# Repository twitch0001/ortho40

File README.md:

# ortho40
 40%  ortho with a display in the middle

Inspired by [ChrisChrisLoLo/keezyboost40](https://github.com/ChrisChrisLoLo/keezyboost40)  (i just need more keys lol)

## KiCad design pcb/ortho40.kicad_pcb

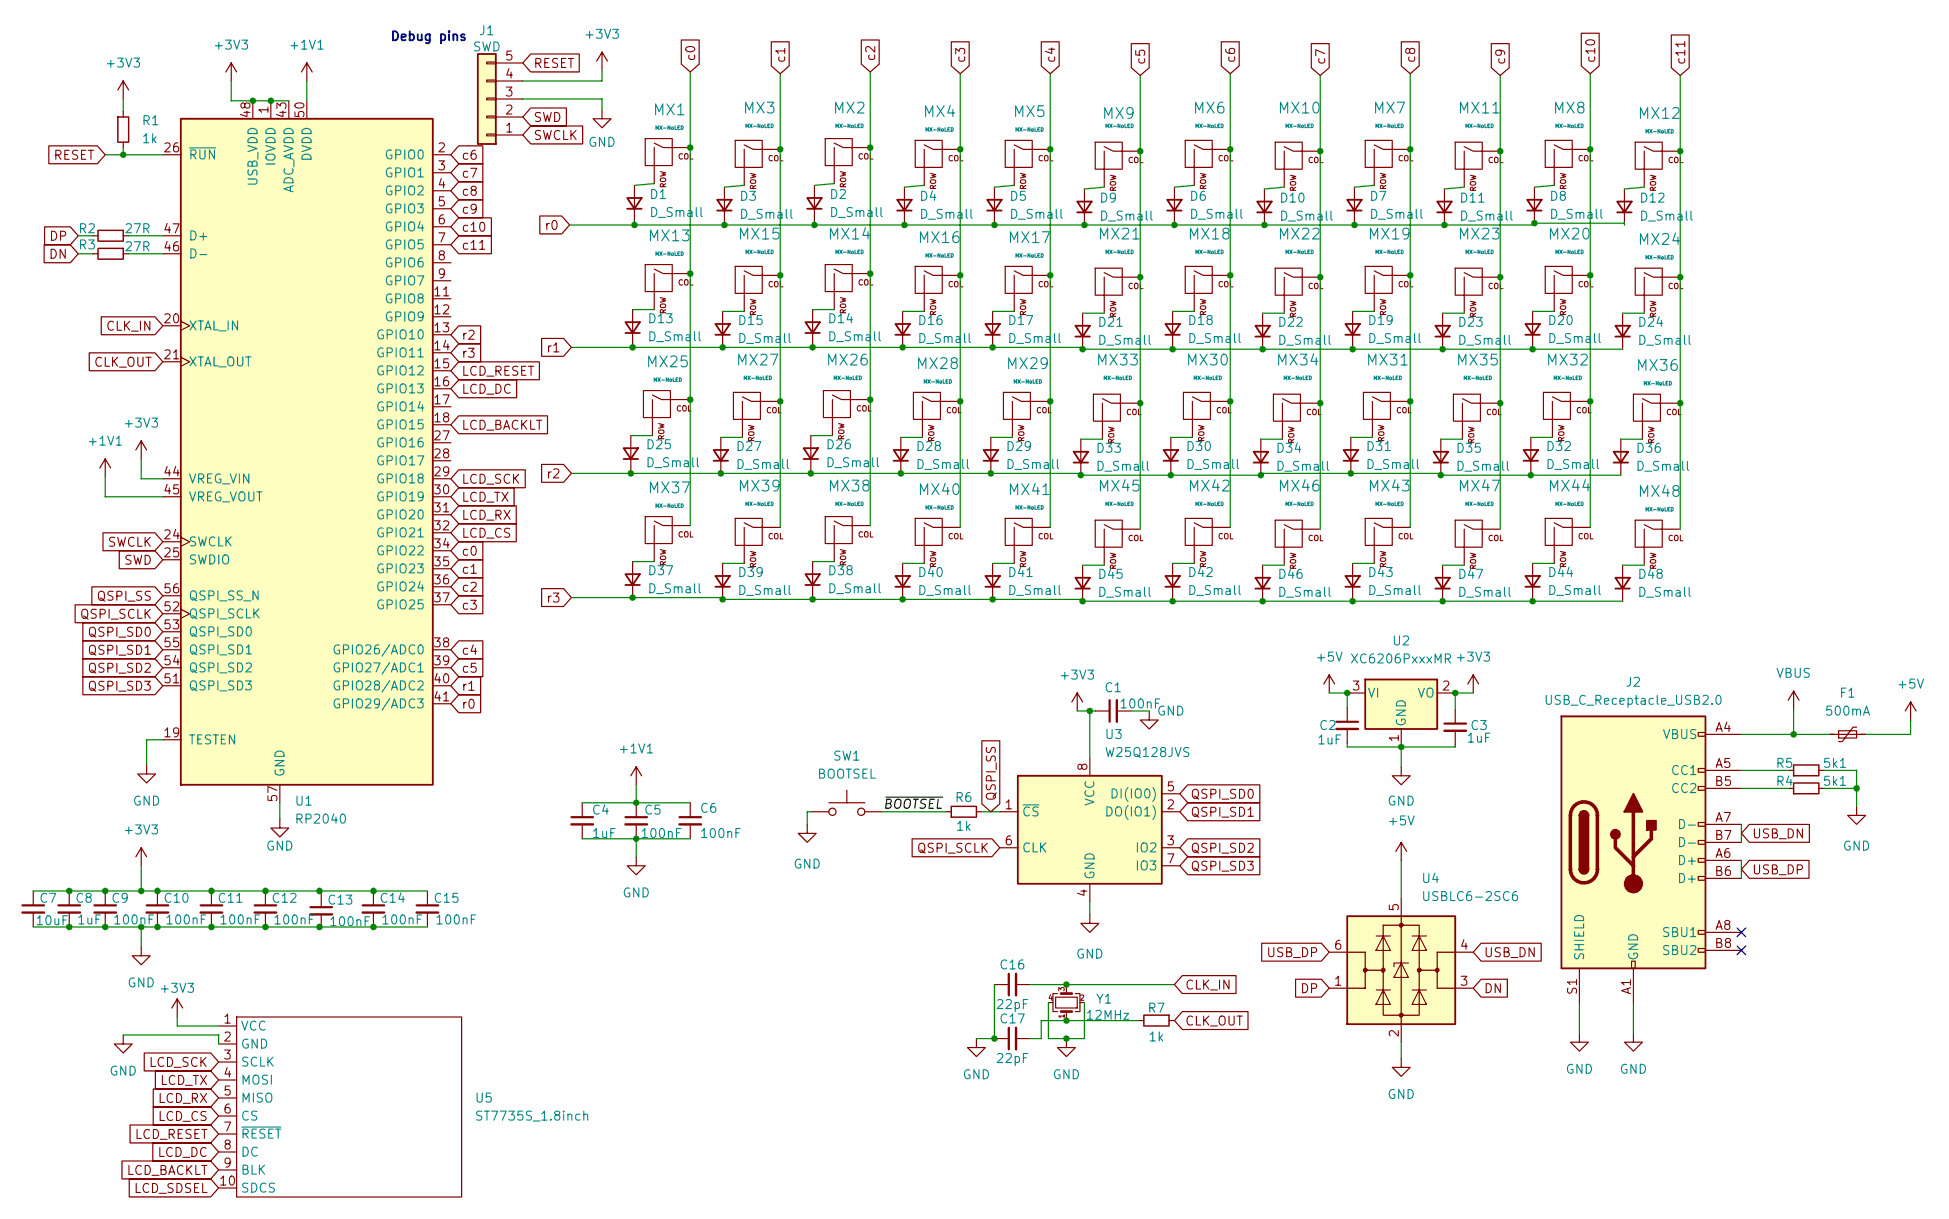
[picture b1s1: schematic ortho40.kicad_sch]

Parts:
C1, C5, C6, C9, C10, C11, C12, C13, C14, C15: 100nF; C_0402_1005Metric
C2, C3, C4, C8: 1uF; C_0402_1005Metric
C7: 10uF; C_0402_1005Metric
C16, C17: 22pF; C_0402_1005Metric
D1, D2, D3, D4, D5, D6, D7, D8, D9, D10, D11, D12, D13, D14, D15, D16, D17, D18, D19, D20, D21, D22, D23, D24, D25, D26, D27, D28, D29, D30, D31, D32, D33, D34, D35, D36, D37, D38, D39, D40, D41, D42, D43, D44, D45, D46, D47, D48: D_Small; D_SOD-123
F1: 500mA; Fuse_1206_3216Metric
J1: SWD; PinSocket_1x05_P2.54mm_Vertical
J2: USB_C_Receptacle_USB2.0; USB_C_Receptacle_HRO_TYPE-C-31-M-12
MX1, MX2, MX3, MX4, MX5, MX6, MX7, MX8, MX9, MX10, MX11, MX12, MX13, MX14, MX15, MX16, MX17, MX18, MX19, MX20, MX21, MX22, MX23, MX24, MX25, MX26, MX27, MX28, MX29, MX30, MX31, MX32, MX33, MX34, MX35, MX36, MX37, MX38, MX39, MX40, MX41, MX42, MX43, MX44, MX45, MX46, MX47, MX48: MX-NoLED; MX-1U-NoLED
R1, R6, R7: 1k; R_0402_1005Metric
R2, R3: 27R; R_0402_1005Metric
R4, R5: 5k1; R_0402_1005Metric
SW1: BOOTSEL; SW_Push_SPST_NO_Alps_SKRK
U1: RP2040; RP2040-QFN-56
U2: XC6206PxxxMR; SOT-23
U3: W25Q128JVS; SOIC-8_5.23x5.23mm_P1.27mm
U4: USBLC6-2SC6; SOT-23-6
U5: ST7735S_1.8inch; DFR0928
Y1: 12MHz; Crystal_SMD_3225-4Pin_3.2x2.5mm

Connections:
+1V1: C4.1, C5.1, C6.1, U1.23 (DVDD), U1.45 (VREG_VOUT), U1.50 (DVDD)
+3V3: C1.1, C3.1, C7.1, C8.1, C9.1, C10.1, C11.1, C12.1, C13.1, C14.1, C15.1, J1.4, R1.1, U1.1 (IOVDD), U1.10 (IOVDD), U1.22 (IOVDD), U1.33 (IOVDD), U1.42 (IOVDD), U1.43 (ADC_AVDD), U1.44 (VREG_VIN), U1.48 (USB_VDD), U1.49 (IOVDD), U2.2 (VO), U3.8 (VCC), U5.1 (VCC)
+5V: C2.1, F1.2, U2.3 (VI), U4.5 (VBUS)
/~BOOTSEL: R6.1, SW1.2
CLK_IN: C16.2, U1.20 (XTAL_IN), Y1.3
CLK_OUT: R7.1, U1.21 (XTAL_OUT)
DN: R3.2, U4.3 (I/O2)
DP: R2.2, U4.1 (I/O1)
GND: C1.2, C2.2, C3.2, C4.2, C5.2, C6.2, C7.2, C8.2, C9.2, C10.2, C11.2, C12.2, C13.2, C14.2, C15.2, C16.1, C17.1, J1.3, J2.A1 (GND), J2.A12 (GND), J2.B1 (GND), J2.B12 (GND), J2.S1 (SHIELD), R4.2, R5.2, SW1.1, U1.19 (TESTEN), U1.57 (GND), U2.1 (GND), U3.4 (GND), U4.2 (GND), U5.2 (GND), Y1.2, Y1.4
LCD_BACKLT: U1.18 (GPIO15), U5.9 (BLK)
LCD_CS: U1.32 (GPIO21), U5.6 (CS)
LCD_DC: U1.16 (GPIO13), U5.8 (DC)
LCD_RESET: U1.15 (GPIO12), U5.7 (~RESET)
LCD_RX: U1.31 (GPIO20), U5.5 (MISO)
LCD_SCK: U1.29 (GPIO18), U5.3 (SCLK)
LCD_SDSEL: U5.10 (SDCS)
LCD_TX: U1.30 (GPIO19), U5.4 (MOSI)
unnamed: C17.2, R7.2, Y1.1
unnamed: D1.2 (A), MX1.2 (ROW)
unnamed: D2.2 (A), MX2.2 (ROW)
unnamed: D3.2 (A), MX3.2 (ROW)
unnamed: D4.2 (A), MX4.2 (ROW)
unnamed: D5.2 (A), MX5.2 (ROW)
unnamed: D6.2 (A), MX6.2 (ROW)
unnamed: D7.2 (A), MX7.2 (ROW)
unnamed: D8.2 (A), MX8.2 (ROW)
unnamed: D9.2 (A), MX9.2 (ROW)
unnamed: D10.2 (A), MX10.2 (ROW)
unnamed: D11.2 (A), MX11.2 (ROW)
unnamed: D12.2 (A), MX12.2 (ROW)
unnamed: D13.2 (A), MX13.2 (ROW)
unnamed: D14.2 (A), MX14.2 (ROW)
unnamed: D15.2 (A), MX15.2 (ROW)
unnamed: D16.2 (A), MX16.2 (ROW)
unnamed: D17.2 (A), MX17.2 (ROW)
unnamed: D18.2 (A), MX18.2 (ROW)
unnamed: D19.2 (A), MX19.2 (ROW)
unnamed: D20.2 (A), MX20.2 (ROW)
unnamed: D21.2 (A), MX21.2 (ROW)
unnamed: D22.2 (A), MX22.2 (ROW)
unnamed: D23.2 (A), MX23.2 (ROW)
unnamed: D24.2 (A), MX24.2 (ROW)
unnamed: D25.2 (A), MX25.2 (ROW)
unnamed: D26.2 (A), MX26.2 (ROW)
unnamed: D27.2 (A), MX27.2 (ROW)
unnamed: D28.2 (A), MX28.2 (ROW)
unnamed: D29.2 (A), MX29.2 (ROW)
unnamed: D30.2 (A), MX30.2 (ROW)
unnamed: D31.2 (A), MX31.2 (ROW)
unnamed: D32.2 (A), MX32.2 (ROW)
unnamed: D33.2 (A), MX33.2 (ROW)
unnamed: D34.2 (A), MX34.2 (ROW)
unnamed: D35.2 (A), MX35.2 (ROW)
unnamed: D36.2 (A), MX36.2 (ROW)
unnamed: D37.2 (A), MX37.2 (ROW)
unnamed: D38.2 (A), MX38.2 (ROW)
unnamed: D39.2 (A), MX39.2 (ROW)
unnamed: D40.2 (A), MX40.2 (ROW)
unnamed: D41.2 (A), MX41.2 (ROW)
unnamed: D42.2 (A), MX42.2 (ROW)
unnamed: D43.2 (A), MX43.2 (ROW)
unnamed: D44.2 (A), MX44.2 (ROW)
unnamed: D45.2 (A), MX45.2 (ROW)
unnamed: D46.2 (A), MX46.2 (ROW)
unnamed: D47.2 (A), MX47.2 (ROW)
unnamed: D48.2 (A), MX48.2 (ROW)
unnamed: J2.A5 (CC1), R4.1
unnamed: J2.B5 (CC2), R5.1
unnamed: R2.1, U1.47 (D+)
unnamed: R3.1, U1.46 (D-)
QSPI_SCLK: U1.52 (QSPI_SCLK), U3.6 (CLK)
QSPI_SD0: U1.53 (QSPI_SD0), U3.5 (DI(IO0))
QSPI_SD1: U1.55 (QSPI_SD1), U3.2 (DO(IO1))
QSPI_SD2: U1.54 (QSPI_SD2), U3.3 (IO2)
QSPI_SD3: U1.51 (QSPI_SD3), U3.7 (IO3)
QSPI_SS: R6.2, U1.56 (QSPI_SS_N), U3.1 (~CS)
RESET: J1.5, R1.2, U1.26 (~RUN)
SWCLK: J1.1, U1.24 (SWCLK)
SWD: J1.2, U1.25 (SWDIO)
USB_DN: J2.A7 (D-), J2.B7 (D-), U4.4 (I/O2)
USB_DP: J2.A6 (D+), J2.B6 (D+), U4.6 (I/O1)
VBUS: F1.1, J2.A4 (VBUS), J2.A9 (VBUS), J2.B4 (VBUS), J2.B9 (VBUS)
c0: MX1.1 (COL), MX13.1 (COL), MX25.1 (COL), MX37.1 (COL), U1.34 (GPIO22)
c1: MX3.1 (COL), MX15.1 (COL), MX27.1 (COL), MX39.1 (COL), U1.35 (GPIO23)
c2: MX2.1 (COL), MX14.1 (COL), MX26.1 (COL), MX38.1 (COL), U1.36 (GPIO24)
c3: MX4.1 (COL), MX16.1 (COL), MX28.1 (COL), MX40.1 (COL), U1.37 (GPIO25)
c4: MX5.1 (COL), MX17.1 (COL), MX29.1 (COL), MX41.1 (COL), U1.38 (GPIO26/ADC0)
c5: MX9.1 (COL), MX21.1 (COL), MX33.1 (COL), MX45.1 (COL), U1.39 (GPIO27/ADC1)
c6: MX6.1 (COL), MX18.1 (COL), MX30.1 (COL), MX42.1 (COL), U1.2 (GPIO0)
c7: MX10.1 (COL), MX22.1 (COL), MX34.1 (COL), MX46.1 (COL), U1.3 (GPIO1)
c8: MX7.1 (COL), MX19.1 (COL), MX31.1 (COL), MX43.1 (COL), U1.4 (GPIO2)
c9: MX11.1 (COL), MX23.1 (COL), MX35.1 (COL), MX47.1 (COL), U1.5 (GPIO3)
c10: MX8.1 (COL), MX20.1 (COL), MX32.1 (COL), MX44.1 (COL), U1.6 (GPIO4)
c11: MX12.1 (COL), MX24.1 (COL), MX36.1 (COL), MX48.1 (COL), U1.7 (GPIO5)
r0: D1.1 (K), D2.1 (K), D3.1 (K), D4.1 (K), D5.1 (K), D6.1 (K), D7.1 (K), D8.1 (K), D9.1 (K), D10.1 (K), D11.1 (K), D12.1 (K), U1.41 (GPIO29/ADC3)
r1: D13.1 (K), D14.1 (K), D15.1 (K), D16.1 (K), D17.1 (K), D18.1 (K), D19.1 (K), D20.1 (K), D21.1 (K), D22.1 (K), D23.1 (K), D24.1 (K), U1.40 (GPIO28/ADC2)
r2: D25.1 (K), D26.1 (K), D27.1 (K), D28.1 (K), D29.1 (K), D30.1 (K), D31.1 (K), D32.1 (K), D33.1 (K), D34.1 (K), D35.1 (K), D36.1 (K), U1.13 (GPIO10)
r3: D37.1 (K), D38.1 (K), D39.1 (K), D40.1 (K), D41.1 (K), D42.1 (K), D43.1 (K), D44.1 (K), D45.1 (K), D46.1 (K), D47.1 (K), D48.1 (K), U1.14 (GPIO11)

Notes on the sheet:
Debug pins

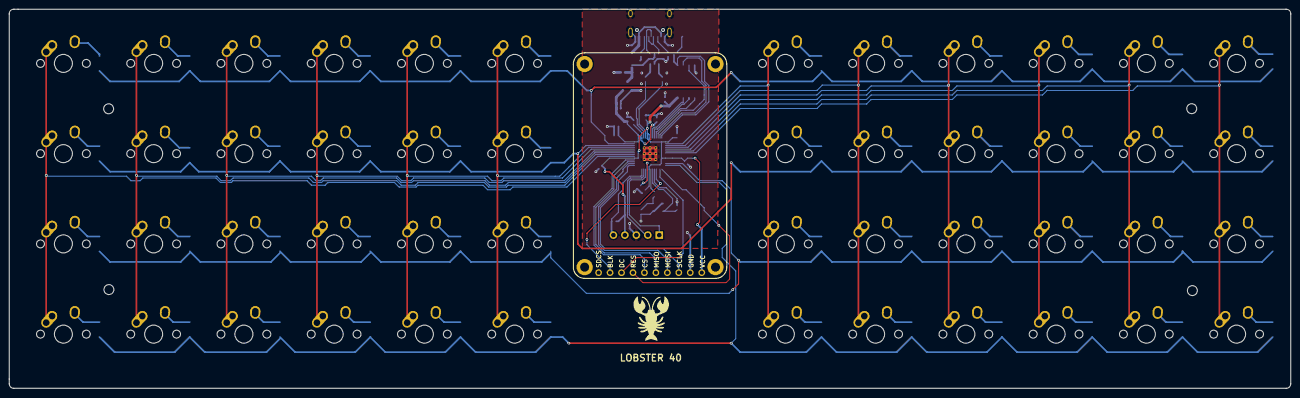
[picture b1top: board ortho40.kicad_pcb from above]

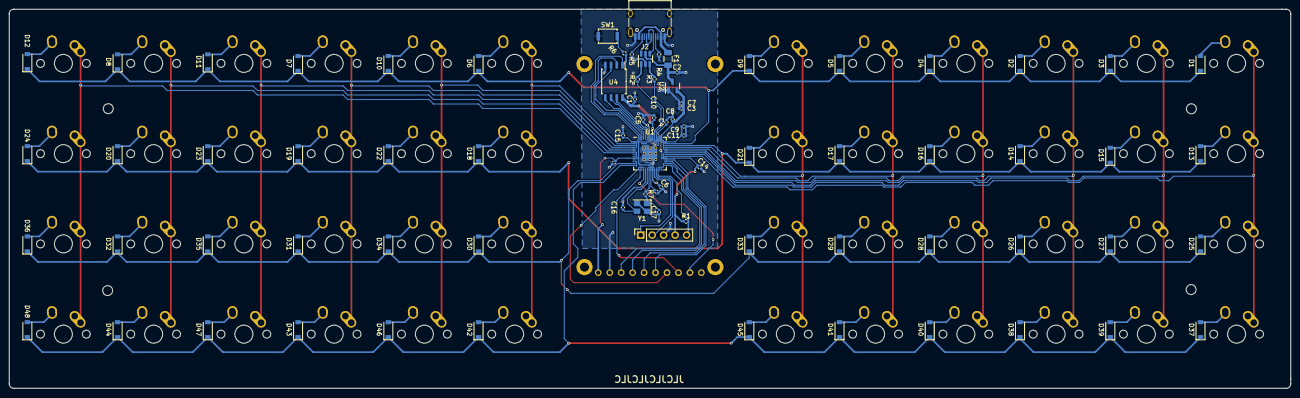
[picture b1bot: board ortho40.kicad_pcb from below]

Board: 2 copper layers, 284.0 x 84.0 mm, 134 parts (81 on the bottom side), 97 nets.

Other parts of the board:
MH1, MH2, MH3, MH4: MountingHole_2.2mm_M2

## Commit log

2022-08-17 Init kicad project
2022-08-17 Add submodules
2022-08-17 Import footprints
2022-08-17 Finish Matrix + Start RP2040 setup
2022-08-18 Schematic done
2022-08-19 blobpain
2022-08-21 Kindof finish pcb
2022-08-21 Move some things
2022-08-22 Fully finish PCB
2022-08-23 Setup Display
2022-08-23 Possibly fix nets?
    I'm not sure but the top pin for +3v3 is still funky :(
2022-08-23 Some net problems again ugh!
2022-08-23 Add track just in case
2022-09-05 Updates...
2022-09-05 Update Display footprint
2022-09-05 More changes...
2022-09-06 Missing connection...
2022-09-15 Use the correct footprint for the display
2022-09-18 Clean up silkscreen
2022-09-19 Finishing touches for rev 2
